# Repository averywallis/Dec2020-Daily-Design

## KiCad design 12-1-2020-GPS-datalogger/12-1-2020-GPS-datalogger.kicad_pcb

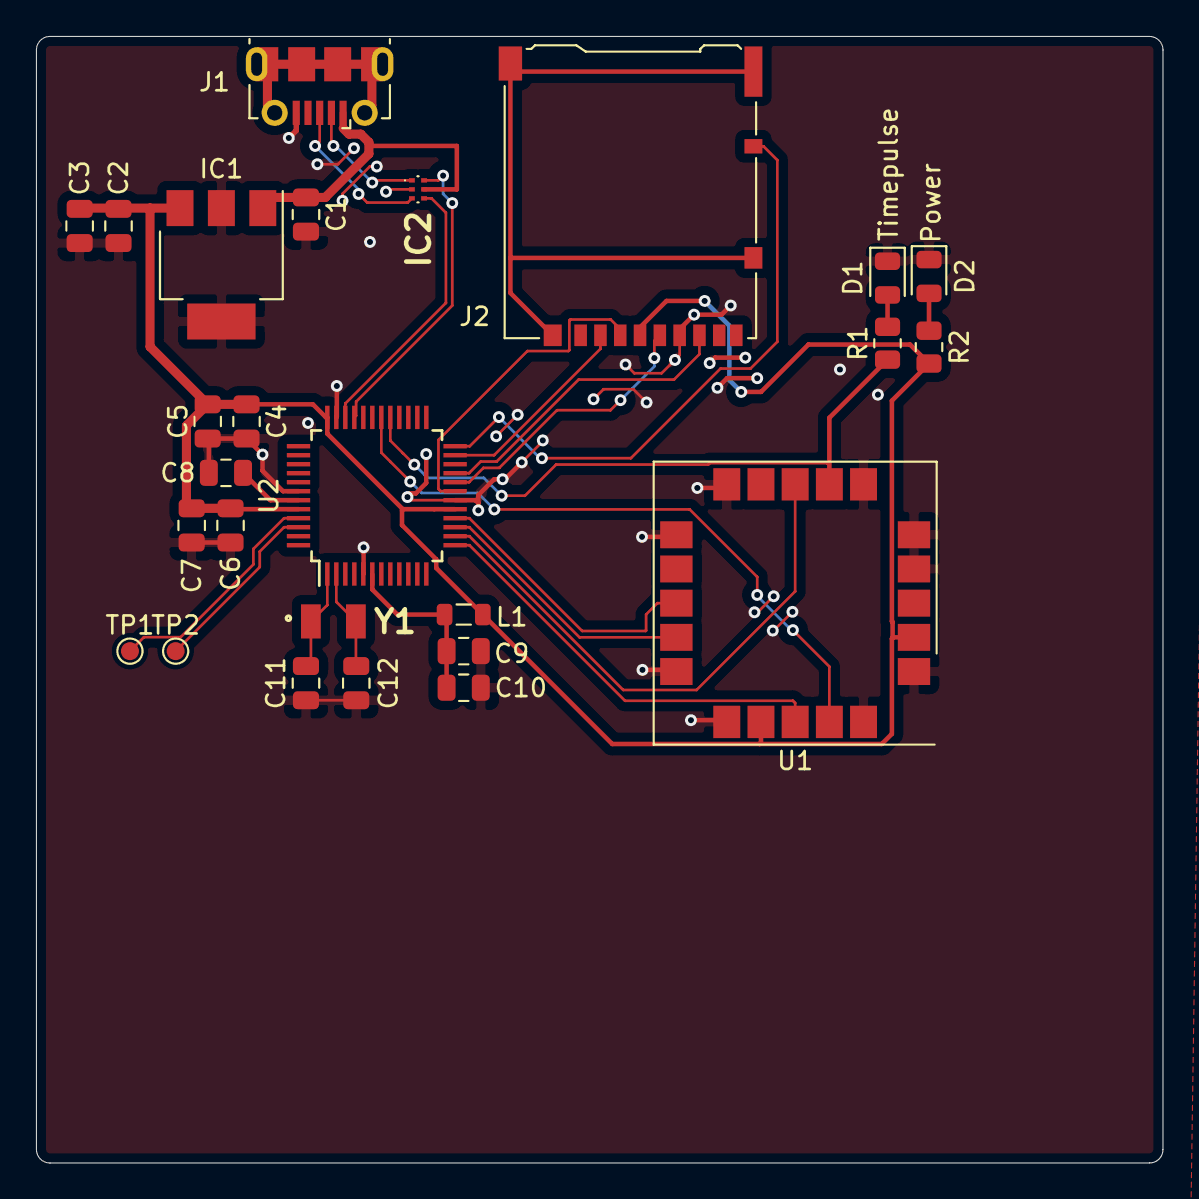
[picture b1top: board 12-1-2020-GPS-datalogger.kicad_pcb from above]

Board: 2 copper layers, 62.6 x 62.6 mm, 26 parts (0 on the bottom side), 26 nets.

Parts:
C1, C2, C8: 1uF; C_0805_2012Metric
C3, C5, C7, C10: 0.1uF; C_0805_2012Metric
C4, C6, C9: 10uF; C_0805_2012Metric
C11, C12: 7pF; C_0805_2012Metric
D1: GREEN; LED_0805_2012Metric
D2: RED; LED_0805_2012Metric
IC1: MIC39100-3.3WS; SOT-223
IC2: PRTR5V0U2F,115; 74LVC1G27GM115
J1: USB_B_Micro; USB_Micro-B_Molex-105017-0001
J2: Micro_SD_Card_Det; microSD_HC_Hirose_DM3AT-SF-PEJM5
L1: 10uH; L_0805_2012Metric
R1, R2: 330; R_0805_2012Metric
TP1, TP2: TestPoint; TestPoint_Pad_D1.0mm
U1: ublox_SAM-M8Q
U2: ATSAMD21G18A-AUT-MCU_Microchip_SAMD; TQFP-48_7x7mm_P0.5mm
Y1: 32.764kHz; ABS-07

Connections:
+3V3: C2.1, C3.1, C4.1, C5.1, C6.1, C7.1, IC1.3, J2.4, L1.2, R2.1, U1.2, U1.17, U2.17, U2.36, U2.44
+5V: C1.1, IC1.1, IC2.5, J1.1
/CD: J2.10, U2.24
/EXTINT: U1.19, U2.30
/MISO: J2.7, U2.21
/MOSI: J2.3, U2.19
/RX: U1.13, U2.16
/SCK: J2.5, U2.20
/SWCLK: TP1.1, U2.45
/SWDIO: TP2.1, U2.46
/TIMEPULSE: R1.1, U1.7, U2.29
/TX: U1.14, U2.15
/USB_D+: IC2.4, U2.34
/USB_D-: IC2.6, U2.33
/sd~CS: J2.2, U2.23
/~GPS_RESET: U1.18, U2.13
/~SAFEBOOT: U1.8, U2.14
GND: C1.2, C2.2, C3.2, C4.2, C5.2, C6.2, C7.2, C8.2, C9.2, C10.2, C11.1, C12.1, D1.1, D2.1, IC1.2, IC1.4, IC2.2, J1.5, J2.6, U1.1, U1.4, U1.5, U1.6, U1.10, U1.11, U1.15, U1.16, U1.20, U2.5, U2.18, U2.35, U2.42
unnamed: C8.1, U2.43
unnamed: C9.1, C10.1, L1.1, U2.6
unnamed: C11.2, U2.1, Y1.1
unnamed: C12.2, U2.2, Y1.2
unnamed: D1.2, R1.2
unnamed: D2.2, R2.2
unnamed: IC2.1, J1.2
unnamed: IC2.3, J1.3

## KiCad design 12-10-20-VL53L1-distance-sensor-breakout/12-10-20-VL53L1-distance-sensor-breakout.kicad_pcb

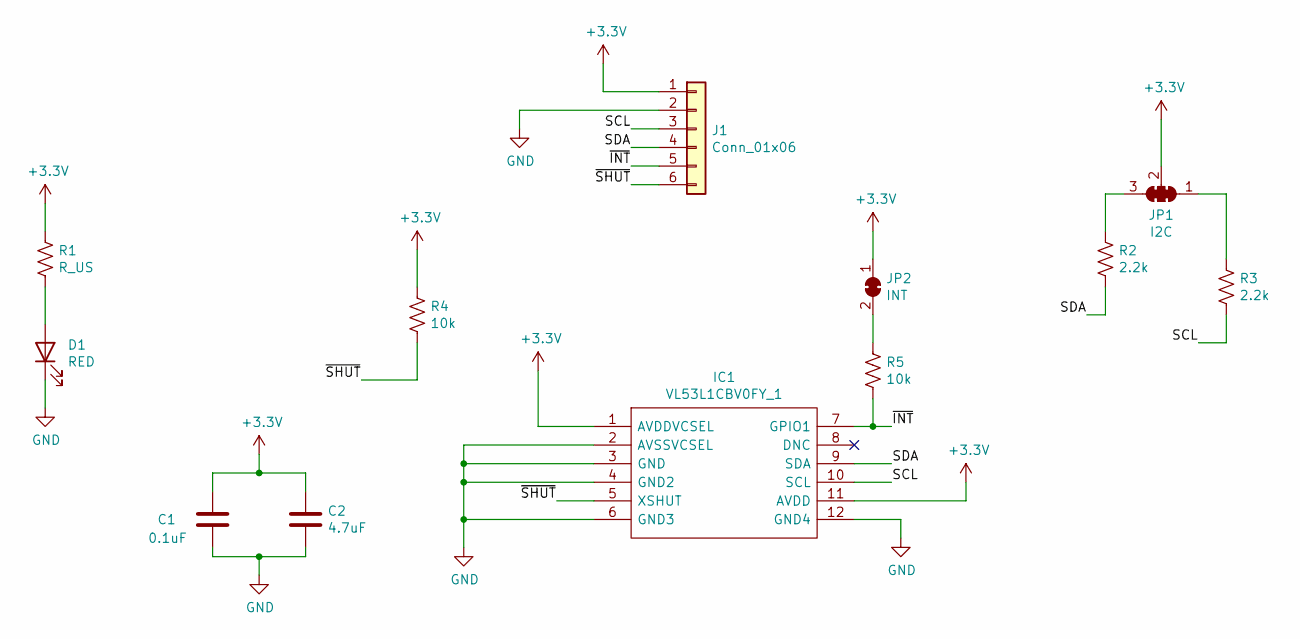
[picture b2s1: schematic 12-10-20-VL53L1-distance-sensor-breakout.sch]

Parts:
C1: 0.1uF; C_0805_2012Metric
C2: 4.7uF; C_0805_2012Metric
D1: RED; LED_0805_2012Metric
IC1: VL53L1CBV0FY_1; VL53L1CBV0FY1; Manufacturer_Part_Number VL53L1CBV0FY/1; Mouser Part Number 511-VL53L1CBV0FY/1
J1: Conn_01x06; PinHeader_1x06_P2.54mm_Vertical
JP1: I2C; SMT-JUMPER_3_2-NC_TRACE_SILK
JP2: INT; SolderJumper-2_P1.3mm_Bridged_Pad1.0x1.5mm
R1: R_US; R_0805_2012Metric
R2, R3: 2.2k; R_0805_2012Metric
R4, R5: 10k; R_0805_2012Metric

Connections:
+3V3: C1.1, C2.1, IC1.1 (AVDDVCSEL), IC1.11 (AVDD), J1.1, JP1.2 (C), JP2.1 (A), R1.1, R4.1
/SCL: IC1.10 (SCL), J1.3, R3.2
/SDA: IC1.9 (SDA), J1.4, R2.2
/~INT: IC1.7 (GPIO1), J1.5, R5.2
/~SHUT: IC1.5 (XSHUT), J1.6, R4.2
GND: C1.2, C2.2, D1.1 (K), IC1.2 (AVSSVCSEL), IC1.3 (GND), IC1.4 (GND2), IC1.6 (GND3), IC1.12 (GND4), J1.2
unnamed: D1.2 (A), R1.2
unnamed: JP1.1 (A), R3.1
unnamed: JP1.3 (B), R2.1
unnamed: JP2.2 (B), R5.1

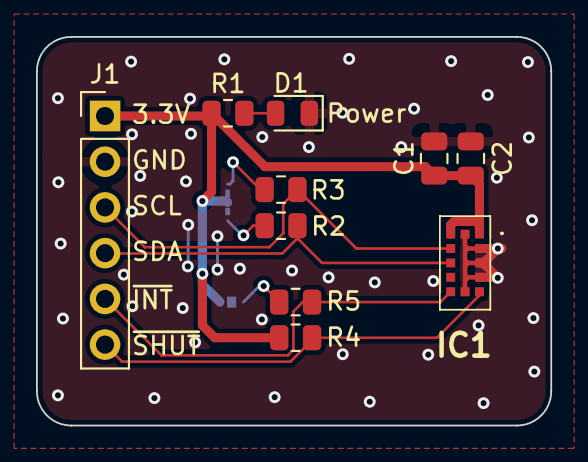
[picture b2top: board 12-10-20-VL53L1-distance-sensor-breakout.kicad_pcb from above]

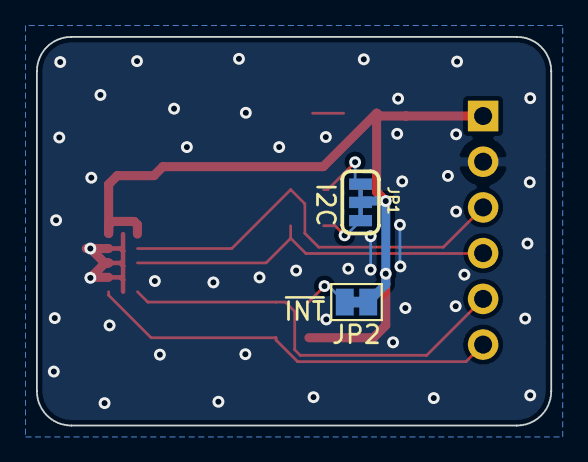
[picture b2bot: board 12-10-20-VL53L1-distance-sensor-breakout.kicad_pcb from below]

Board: 2 copper layers, 28.6 x 21.6 mm, 12 parts (2 on the bottom side), 10 nets.

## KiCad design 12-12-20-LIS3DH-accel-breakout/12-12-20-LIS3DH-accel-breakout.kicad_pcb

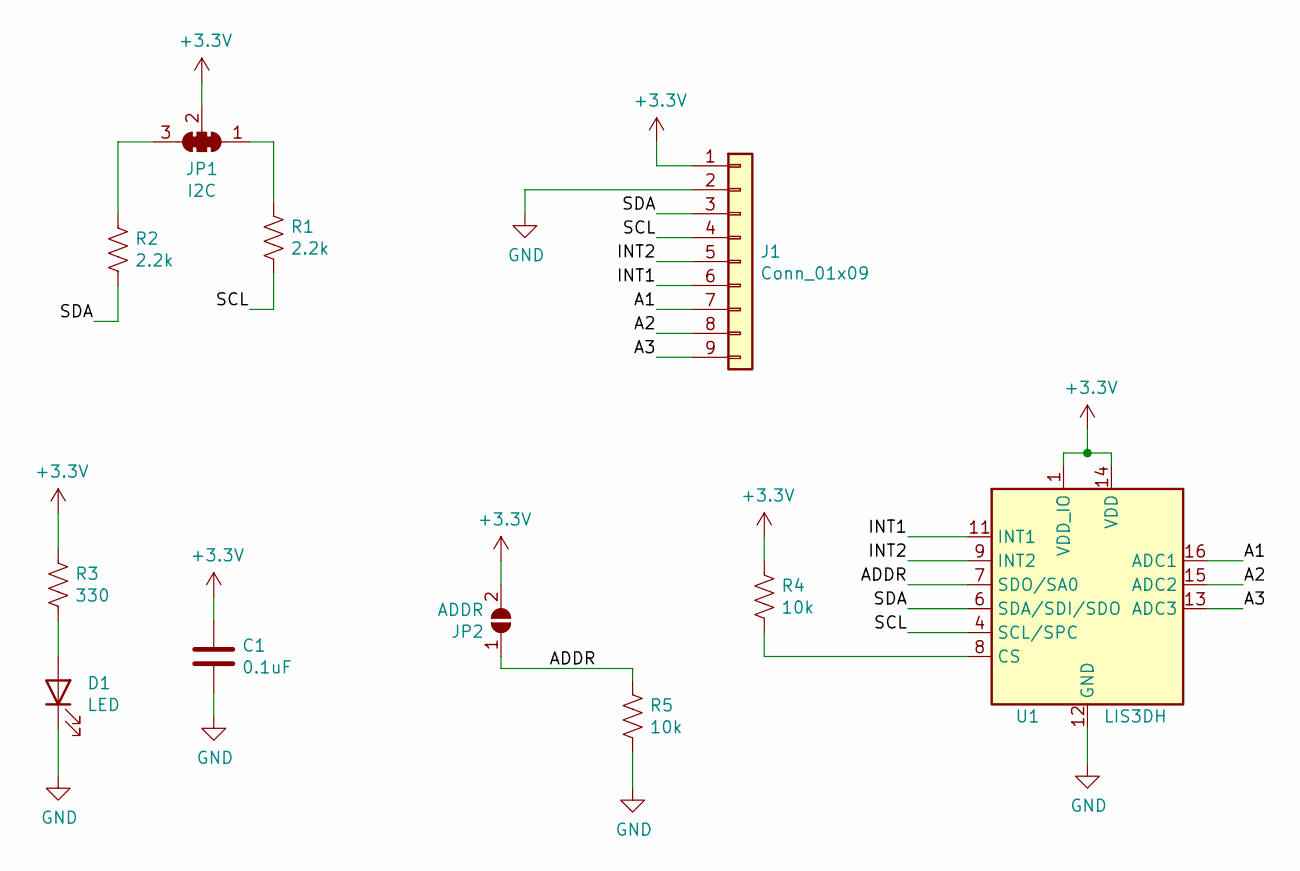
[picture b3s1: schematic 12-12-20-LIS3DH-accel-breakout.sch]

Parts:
C1: 0.1uF; C_0805_2012Metric
D1: LED; LED_0805_2012Metric
J1: Conn_01x09; PinHeader_1x09_P2.54mm_Vertical
JP1: I2C; SMT-JUMPER_3_2-NC_TRACE_SILK
JP2: ADDR; SolderJumper-2_P1.3mm_Open_RoundedPad1.0x1.5mm
R1, R2: 2.2k; R_0805_2012Metric
R3: 330; R_0805_2012Metric
R4, R5: 10k; R_0805_2012Metric
U1: LIS3DH; LGA-16_3x3mm_P0.5mm_LayoutBorder3x5y

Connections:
+3V3: C1.1, J1.1, JP1.2 (C), JP2.2 (B), R3.1, R4.1, U1.1 (VDD_IO), U1.14 (VDD)
/A1: J1.7, U1.16 (ADC1)
/A2: J1.8, U1.15 (ADC2)
/A3: J1.9, U1.13 (ADC3)
/ADDR: JP2.1 (A), R5.1, U1.7 (SDO/SA0)
/INT1: J1.6, U1.11 (INT1)
/INT2: J1.5, U1.9 (INT2)
/SCL: J1.4, R1.2, U1.4 (SCL/SPC)
/SDA: J1.3, R2.2, U1.6 (SDA/SDI/SDO)
GND: C1.2, D1.1 (K), J1.2, R5.2, U1.5 (GND), U1.10 (GND), U1.12 (GND)
unnamed: D1.2 (A), R3.2
unnamed: JP1.1 (A), R1.1
unnamed: JP1.3 (B), R2.1
unnamed: R4.2, U1.8 (CS)

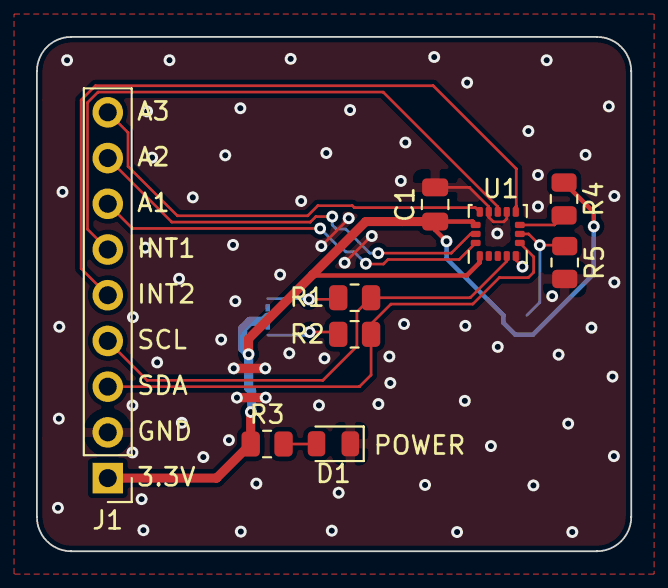
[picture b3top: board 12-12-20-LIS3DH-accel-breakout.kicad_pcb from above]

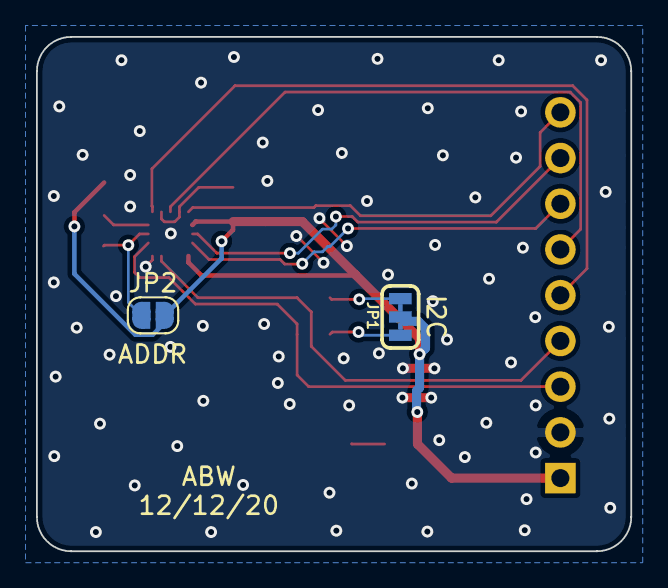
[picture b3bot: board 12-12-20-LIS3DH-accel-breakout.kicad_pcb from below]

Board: 2 copper layers, 33.0 x 28.6 mm, 11 parts (2 on the bottom side), 14 nets.

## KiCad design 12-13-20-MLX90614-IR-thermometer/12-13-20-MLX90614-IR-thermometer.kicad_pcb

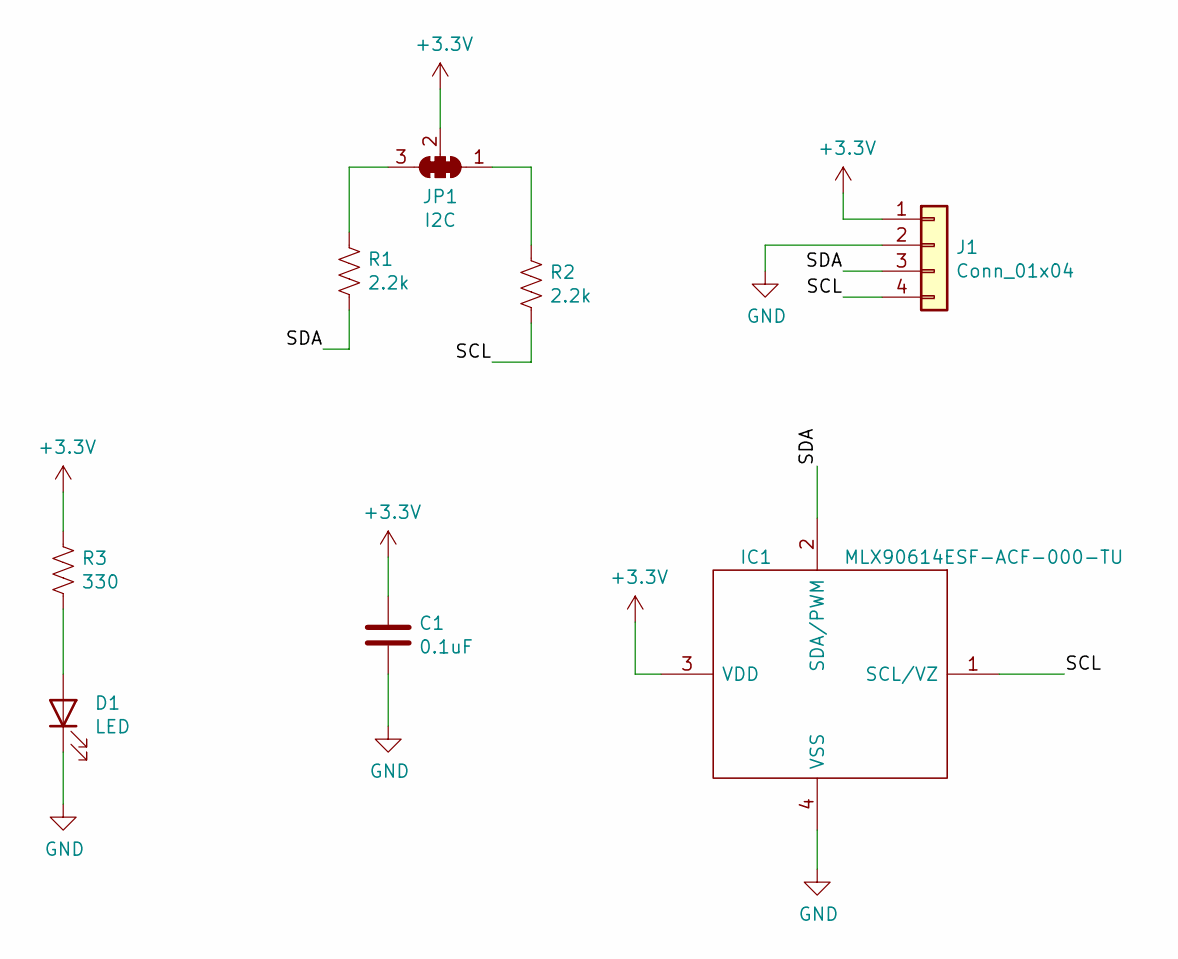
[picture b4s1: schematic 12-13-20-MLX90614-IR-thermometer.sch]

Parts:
C1: 0.1uF; C_0805_2012Metric
D1: LED; LED_0805_2012Metric
IC1: MLX90614ESF-ACF-000-TU; MLX90614ESFDCC000SP; Manufacturer_Part_Number MLX90614ESF-ACF-000-TU; Mouser Part Number 482-90614ESFACF000TU
J1: Conn_01x04; PinHeader_1x04_P2.54mm_Vertical
JP1: I2C; SMT-JUMPER_3_2-NC_TRACE_SILK
R1, R2: 2.2k; R_0805_2012Metric
R3: 330; R_0805_2012Metric

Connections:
+3V3: C1.1, IC1.3 (VDD), J1.1, JP1.2 (C), R3.1
/SCL: IC1.1 (SCL/VZ), J1.4, R2.2
/SDA: IC1.2 (SDA/PWM), J1.3, R1.2
GND: C1.2, D1.1 (K), IC1.4 (VSS), J1.2
unnamed: D1.2 (A), R3.2
unnamed: JP1.1 (A), R2.1
unnamed: JP1.3 (B), R1.1

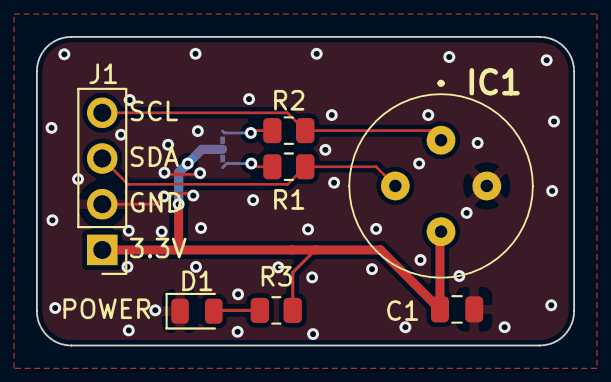
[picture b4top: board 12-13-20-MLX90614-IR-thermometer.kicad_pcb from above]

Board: 2 copper layers, 29.8 x 17.1 mm, 8 parts (1 on the bottom side), 7 nets.

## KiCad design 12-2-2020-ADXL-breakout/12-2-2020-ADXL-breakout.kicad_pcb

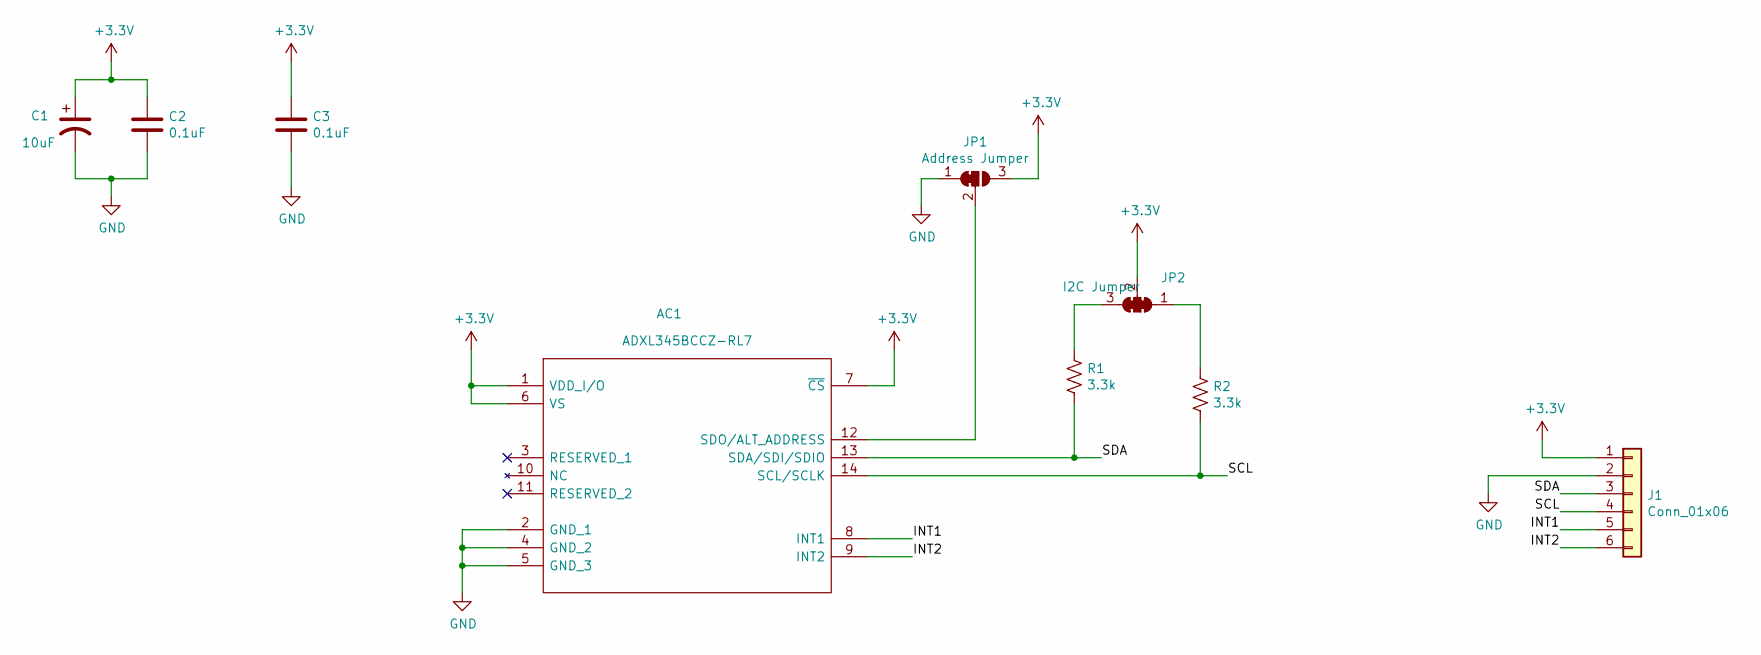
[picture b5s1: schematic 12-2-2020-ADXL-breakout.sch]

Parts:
AC1: ADXL345BCCZ-RL7; LGA-14_3x5mm_P0.8mm_LayoutBorder1x6y; Manufacturer_Part_Number ADXL345BCCZ-RL7; Mouser Part Number 584-ADXL345BCCZ-R7
C1: 10uF; CP_EIA-3528-15_AVX-H
C2, C3: 0.1uF; C_0805_2012Metric
J1: Conn_01x06; PinHeader_1x06_P2.54mm_Vertical
JP1: Address Jumper; SolderJumper-3_P1.3mm_Bridged12_Pad1.0x1.5mm
JP2: I2C Jumper; SMT-JUMPER_3_2-NC_TRACE_SILK
R1, R2: 3.3k; R_0805_2012Metric

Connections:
+3V3: AC1.1 (VDD_I/O), AC1.6 (VS), AC1.7 (~CS), C1.1, C2.1, C3.1, J1.1, JP1.3 (B), JP2.2 (C)
/INT1: AC1.8 (INT1), J1.5
/INT2: AC1.9 (INT2), J1.6
/SCL: AC1.14 (SCL/SCLK), J1.4, R2.2
/SDA: AC1.13 (SDA/SDI/SDIO), J1.3, R1.2
GND: AC1.2 (GND_1), AC1.4 (GND_2), AC1.5 (GND_3), C1.2, C2.2, C3.2, J1.2, JP1.1 (A)
unnamed: AC1.12 (SDO/ALT_ADDRESS), JP1.2 (C)
unnamed: JP2.1 (A), R2.1
unnamed: JP2.3 (B), R1.1

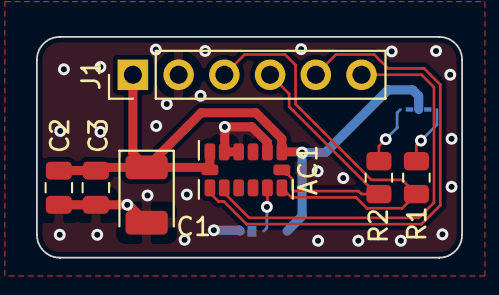
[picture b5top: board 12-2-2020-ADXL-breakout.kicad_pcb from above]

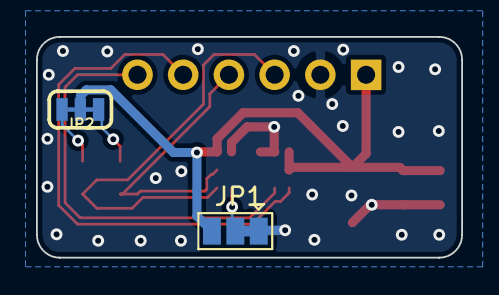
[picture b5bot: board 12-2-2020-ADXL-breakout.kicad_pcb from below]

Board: 2 copper layers, 23.6 x 12.3 mm, 9 parts (2 on the bottom side), 9 nets.

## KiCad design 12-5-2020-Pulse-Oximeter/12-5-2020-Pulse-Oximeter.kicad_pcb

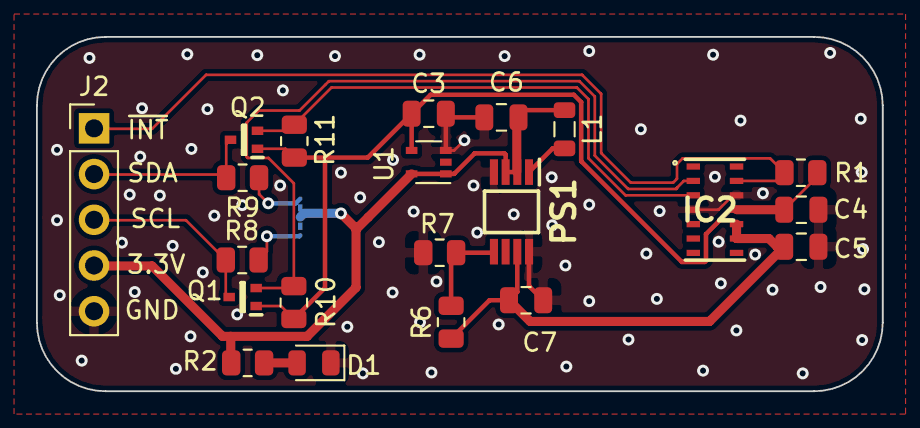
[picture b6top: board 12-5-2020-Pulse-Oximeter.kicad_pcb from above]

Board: 2 copper layers, 47.0 x 19.7 mm, 22 parts (1 on the bottom side), 14 nets.

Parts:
C3: 1.0uF; C_0805_2012Metric
C4: 0.1uF; C_0805_2012Metric
C5, C6: 10uF; C_0805_2012Metric
C7: 22uF; C_0805_2012Metric
D1: LED; LED_0805_2012Metric
IC2: MAX30101EFD+; 14-LEAD-OESIP
J2: Conn_01x05; PinHeader_1x05_P2.54mm_Vertical
JP2: I2C Jumper; SMT-JUMPER_3_2-NC_TRACE_SILK
L1: 2.2uH; L_0805_2012Metric
PS1: PAM2401SCADJ; SOP65P490X110-8N
Q1, Q2: RE1C001UNTCL; SOTFL50P160X85-3N
R1: 4.7k; R_0805_2012Metric
R2: 330; R_0805_2012Metric
R6: 750k; R_0805_2012Metric
R7: 100k; R_0805_2012Metric
R8, R9, R10, R11: 2.2k; R_0805_2012Metric
U1: SP6214; SOT-353_SC-70-5

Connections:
+1V8: C3.1, C4.1, IC2.11, Q1.1, Q2.1, R1.1, R10.1, R11.1, U1.4
+3V3: C6.1, J2.4, JP2.2, L1.1, PS1.2, PS1.3, R2.1, U1.1, U1.5
+5V: C5.1, C7.1, IC2.9, IC2.10, PS1.7, R6.1
/SCL: J2.3, Q1.3, R8.2
/SDA: J2.2, Q2.3, R9.2
/SNSR_SCL: IC2.2, Q1.2, R10.2
/SNSR_SDA: IC2.3, Q2.2, R11.2
/~HR_INT: IC2.13, J2.1, R1.2
GND: C3.2, C4.2, C5.2, C6.2, C7.2, D1.1, IC2.4, IC2.12, J2.5, PS1.4, PS1.8, R7.2, U1.3
unnamed: D1.2, R2.2
unnamed: JP2.1, R8.1
unnamed: JP2.3, R9.1
unnamed: L1.2, PS1.1
unnamed: PS1.5, R6.2, R7.1

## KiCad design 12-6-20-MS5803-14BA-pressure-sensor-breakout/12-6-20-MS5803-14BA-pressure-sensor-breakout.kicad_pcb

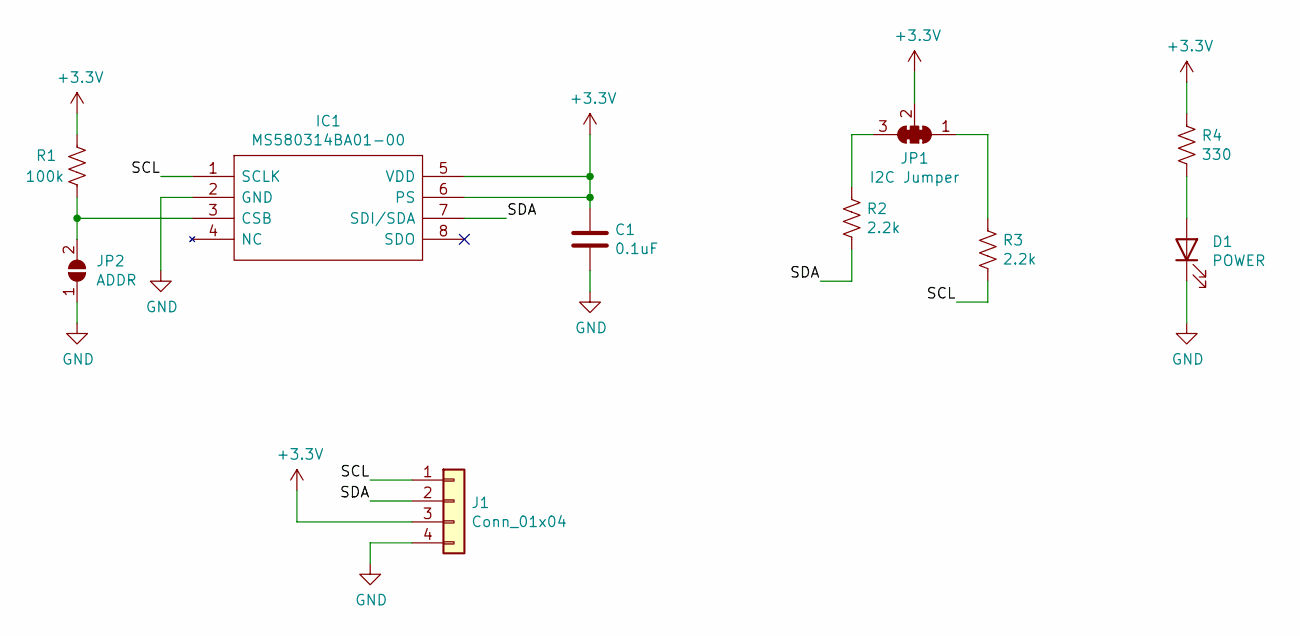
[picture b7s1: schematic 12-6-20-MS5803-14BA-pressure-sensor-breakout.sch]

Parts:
C1: 0.1uF; C_0805_2012Metric
D1: POWER; LED_0805_2012Metric
IC1: MS580314BA01-00; MS580314BA0100; Manufacturer_Part_Number MS580314BA01-00; Mouser Part Number 824-MS580314BA01-00
J1: Conn_01x04; PinHeader_1x04_P2.54mm_Vertical
JP1: I2C Jumper; SMT-JUMPER_3_2-NC_TRACE_SILK
JP2: ADDR; SolderJumper-2_P1.3mm_Open_RoundedPad1.0x1.5mm
R1: 100k; R_0805_2012Metric
R2, R3: 2.2k; R_0805_2012Metric
R4: 330; R_0805_2012Metric

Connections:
+3V3: C1.1, IC1.5 (VDD), IC1.6 (PS), J1.3, JP1.2 (C), R1.1, R4.1
/SCL: IC1.1 (SCLK), J1.1, R3.2
/SDA: IC1.7 (SDI/SDA), J1.2, R2.2
GND: C1.2, D1.1 (K), IC1.2 (GND), J1.4, JP2.1 (A)
unnamed: D1.2 (A), R4.2
unnamed: IC1.3 (CSB), JP2.2 (B), R1.2
unnamed: JP1.1 (A), R3.1
unnamed: JP1.3 (B), R2.1

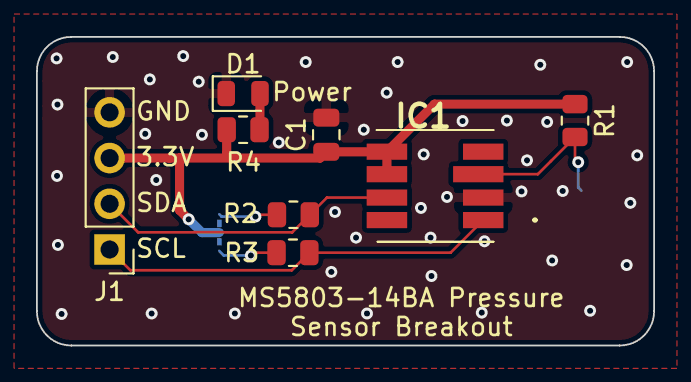
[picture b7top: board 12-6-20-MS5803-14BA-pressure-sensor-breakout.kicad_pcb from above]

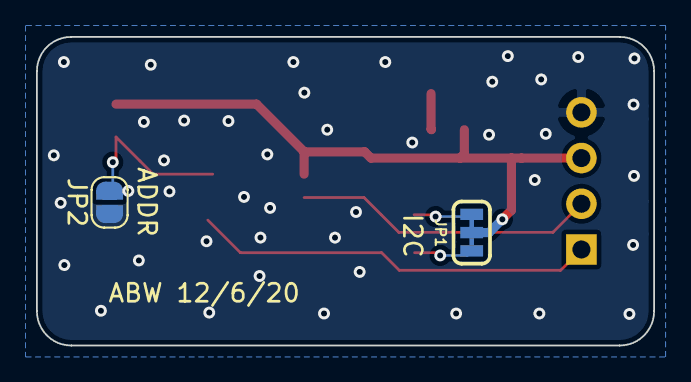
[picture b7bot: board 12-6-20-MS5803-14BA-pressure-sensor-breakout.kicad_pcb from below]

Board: 2 copper layers, 34.3 x 17.1 mm, 10 parts (2 on the bottom side), 8 nets.

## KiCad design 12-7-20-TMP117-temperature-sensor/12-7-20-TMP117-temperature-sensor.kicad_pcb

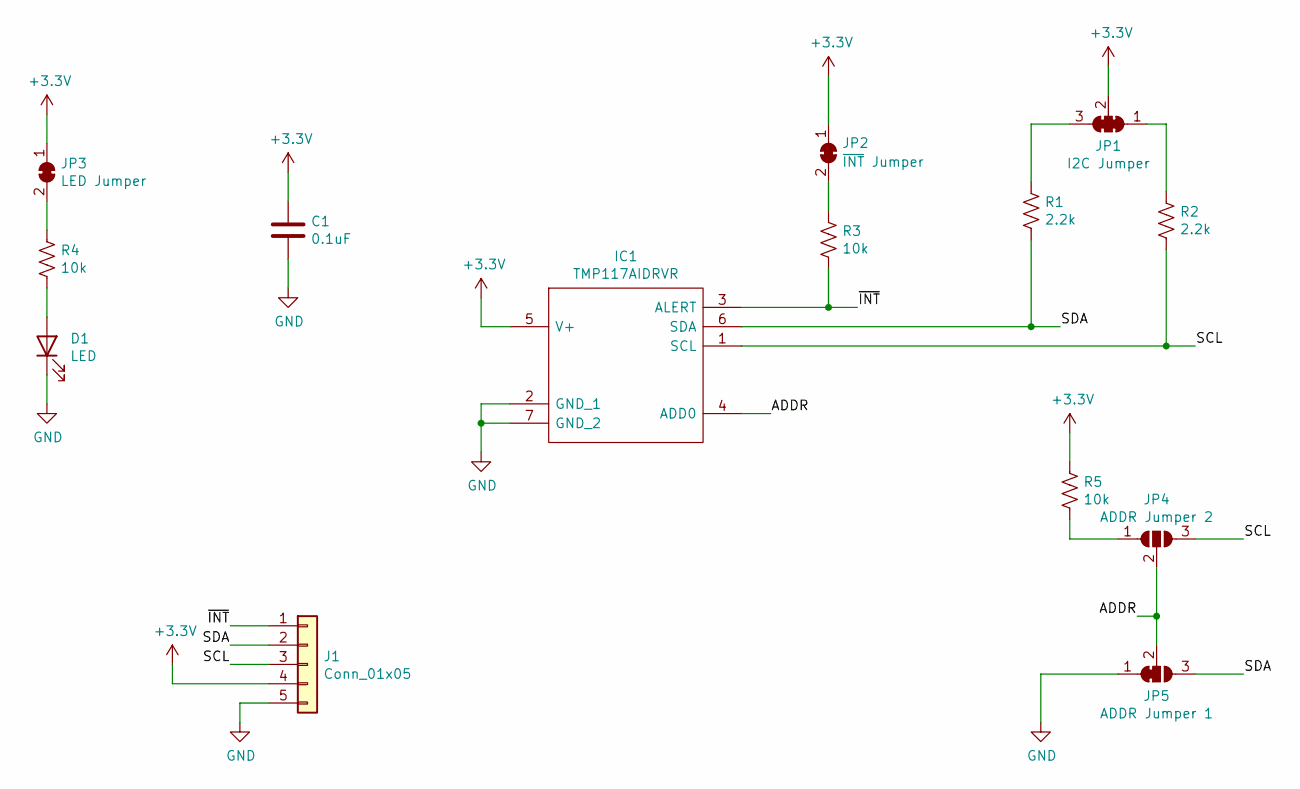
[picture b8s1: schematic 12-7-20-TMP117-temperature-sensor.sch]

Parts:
C1: 0.1uF; C_0805_2012Metric
D1: LED; LED_0805_2012Metric
IC1: TMP117AIDRVR; SON65P200X200X80-7N; Manufacturer_Part_Number TMP117AIDRVR; Mouser Part Number 595-TMP117AIDRVR
J1: Conn_01x05; PinHeader_1x05_P2.54mm_Vertical
JP1: I2C Jumper; SMT-JUMPER_3_2-NC_TRACE_SILK
JP2: ~INT~ Jumper; SolderJumper-2_P1.3mm_Bridged_RoundedPad1.0x1.5mm
JP3: LED Jumper; SolderJumper-2_P1.3mm_Bridged_RoundedPad1.0x1.5mm
JP4: ADDR Jumper 2; SolderJumper-3_P1.3mm_Open_RoundedPad1.0x1.5mm
JP5: ADDR Jumper 1; SolderJumper-3_P1.3mm_Bridged12_RoundedPad1.0x1.5mm
R1, R2: 2.2k; R_0805_2012Metric
R3, R4, R5: 10k; R_0805_2012Metric

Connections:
+3V3: C1.1, IC1.5 (V+), J1.4, JP1.2 (C), JP2.1 (A), JP3.1 (A), R5.1
/ADDR: IC1.4 (ADD0), JP4.2 (C), JP5.2 (C)
/SCL: IC1.1 (SCL), J1.3, JP4.3 (B), R2.2
/SDA: IC1.6 (SDA), J1.2, JP5.3 (B), R1.2
/~INT: IC1.3 (ALERT), J1.1, R3.2
GND: C1.2, D1.1 (K), IC1.2 (GND_1), IC1.7 (GND_2), J1.5, JP5.1 (A)
unnamed: D1.2 (A), R4.2
unnamed: JP1.1 (A), R2.1
unnamed: JP1.3 (B), R1.1
unnamed: JP2.2 (B), R3.1
unnamed: JP3.2 (B), R4.1
unnamed: JP4.1 (A), R5.2

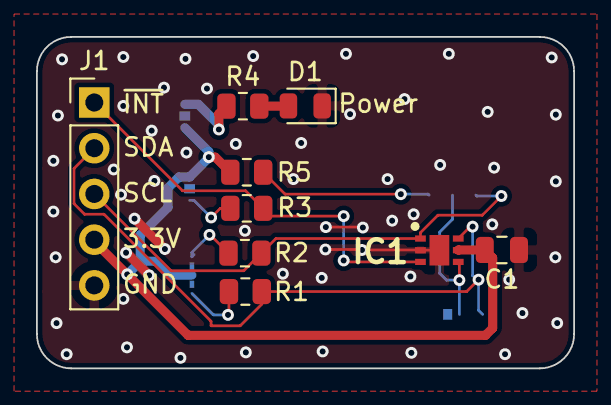
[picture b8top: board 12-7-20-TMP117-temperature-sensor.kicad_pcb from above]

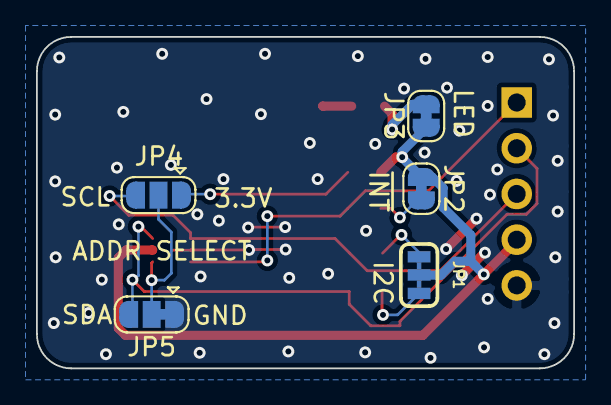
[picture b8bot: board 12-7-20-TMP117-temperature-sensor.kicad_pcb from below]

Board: 2 copper layers, 29.8 x 18.4 mm, 14 parts (5 on the bottom side), 12 nets.
